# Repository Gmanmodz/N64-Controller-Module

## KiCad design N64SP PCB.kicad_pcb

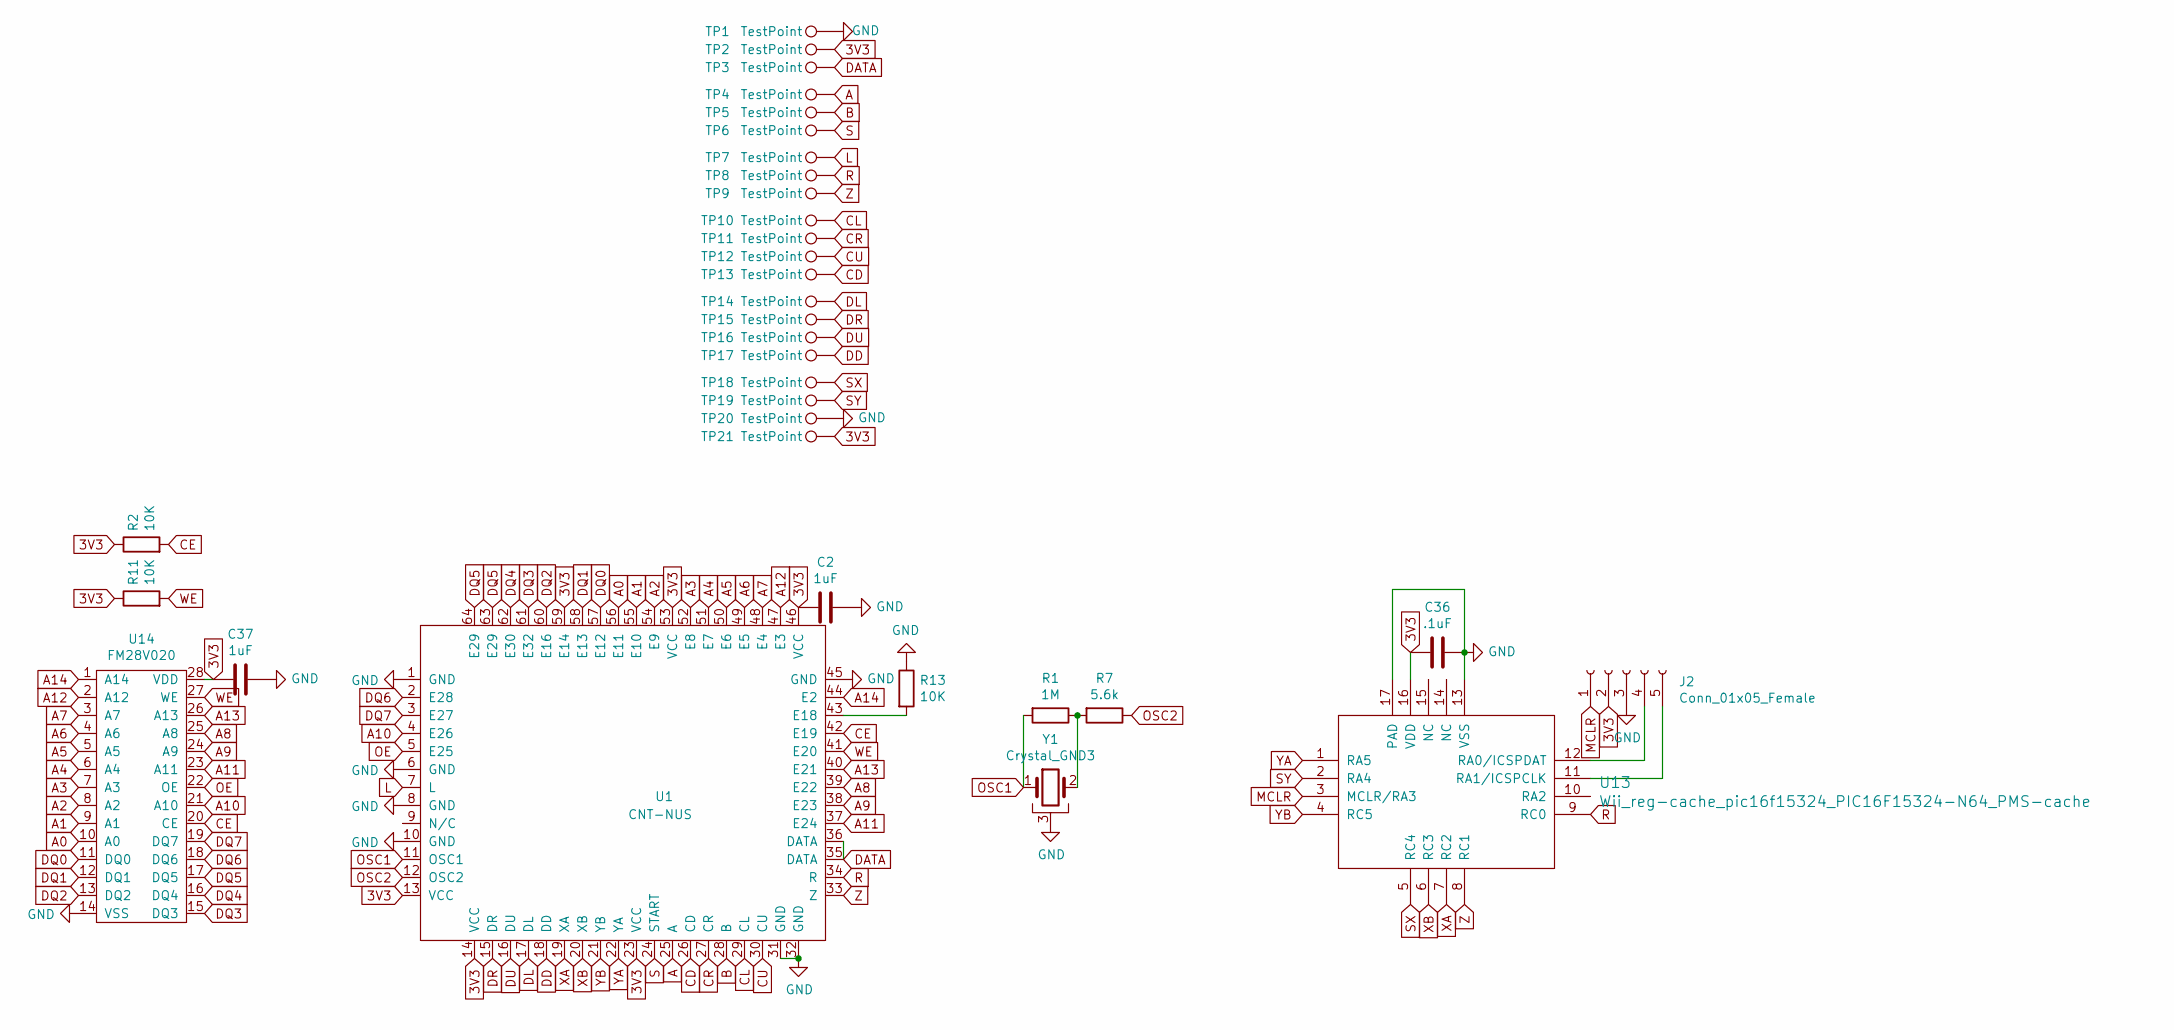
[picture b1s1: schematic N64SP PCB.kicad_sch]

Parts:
C2, C37: 1uF; C_0402_custom
C36: .1uF; C_0402_custom
J2: Conn_01x05_Female; PinHeader_1x05_P2.54mm_Vertical
R1: 1M; R_0402_custom
R2, R11, R13: 10K; R_0402_custom
R7: 5.6k; R_0402_custom
TP1, TP2, TP3, TP4, TP5, TP6, TP7, TP8, TP9, TP10, TP11, TP12, TP13, TP14, TP15, TP16, TP17, TP18, TP19, TP20, TP21: TestPoint; pad_castellated1
U1: CNT-NUS
U13: Wii_reg-cache_pic16f15324_PIC16F15324-N64_PMS-cac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; QFN-16-1EP_4x4mm_P0.65mm_EP2.1x2.1mm
U14: FM28V020; SOIC-28W_7.5x17.9mm_P1.27mm
Y1: Crystal_GND3; NUS-OSC

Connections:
3V3: C2.2, C36.2, C37.2, J2.2, R2.1, R11.1, TP2.1, TP21.1, U1.13 (VCC), U1.14 (VCC), U1.23 (VCC), U1.46 (VCC), U1.53 (VCC), U1.59 (E14), U13.16 (VDD), U14.28 (VDD)
A: TP4.1, U1.25 (A)
A0: U1.56 (E11), U14.10 (A0)
A1: U1.55 (E10), U14.9 (A1)
A2: U1.54 (E9), U14.8 (A2)
A3: U1.52 (E8), U14.7 (A3)
A4: U1.51 (E7), U14.6 (A4)
A5: U1.50 (E6), U14.5 (A5)
A6: U1.49 (E5), U14.4 (A6)
A7: U1.48 (E4), U14.3 (A7)
A8: U1.39 (E22), U14.25 (A8)
A9: U1.38 (E23), U14.24 (A9)
A10: U1.4 (E26), U14.21 (A10)
A11: U1.37 (E24), U14.23 (A11)
A12: U1.47 (E3), U14.2 (A12)
A13: U1.40 (E21), U14.26 (A13)
A14: U1.44 (E2), U14.1 (A14)
B: TP5.1, U1.28 (B)
CD: TP13.1, U1.26 (CD)
CE: R2.2, U1.42 (E19), U14.20 (CE)
CL: TP10.1, U1.29 (CL)
CR: TP11.1, U1.27 (CR)
CU: TP12.1, U1.30 (CU)
DATA: TP3.1, U1.35 (DATA), U1.36 (DATA)
DD: TP17.1, U1.18 (DD)
DL: TP14.1, U1.17 (DL)
DQ0: U1.57 (E12), U14.11 (DQ0)
DQ1: U1.58 (E13), U14.12 (DQ1)
DQ2: U1.60 (E16), U14.13 (DQ2)
DQ3: U1.61 (E32), U14.15 (DQ3)
DQ4: U1.62 (E30), U14.16 (DQ4)
DQ5: U1.63 (E29), U1.64 (E29), U14.17 (DQ5)
DQ6: U1.2 (E28), U14.18 (DQ6)
DQ7: U1.3 (E27), U14.19 (DQ7)
DR: TP15.1, U1.15 (DR)
DU: TP16.1, U1.16 (DU)
GND: C2.1, C36.1, C37.1, J2.3, R13.1, TP1.1, TP20.1, U1.1 (GND), U1.6 (GND), U1.8 (GND), U1.10 (GND), U1.31 (GND), U1.32 (GND), U1.45 (GND), U13.13 (VSS), U13.17 (PAD), U14.14 (VSS), Y1.3
L: TP7.1, U1.7 (L)
MCLR: J2.1, U13.3 (MCLR/RA3)
unnamed: J2.4, U13.12 (RA0/ICSPDAT)
unnamed: J2.5, U13.11 (RA1/ICSPCLK)
unnamed: R1.1, R7.2, Y1.2
unnamed: R13.2, U1.43 (E18)
OE: U1.5 (E25), U14.22 (OE)
OSC1: R1.2, U1.11 (OSC1), Y1.1
OSC2: R7.1, U1.12 (OSC2)
R: TP8.1, U1.34 (R), U13.9 (RC0)
S: TP6.1, U1.24 (START)
SX: TP18.1, U13.5 (RC4)
SY: TP19.1, U13.2 (RA4)
WE: R11.2, U1.41 (E20), U14.27 (WE)
XA: U1.19 (XA), U13.7 (RC2)
XB: U1.20 (XB), U13.6 (RC3)
YA: U1.22 (YA), U13.1 (RA5)
YB: U1.21 (YB), U13.4 (RC5)
Z: TP9.1, U1.33 (Z), U13.8 (RC1)

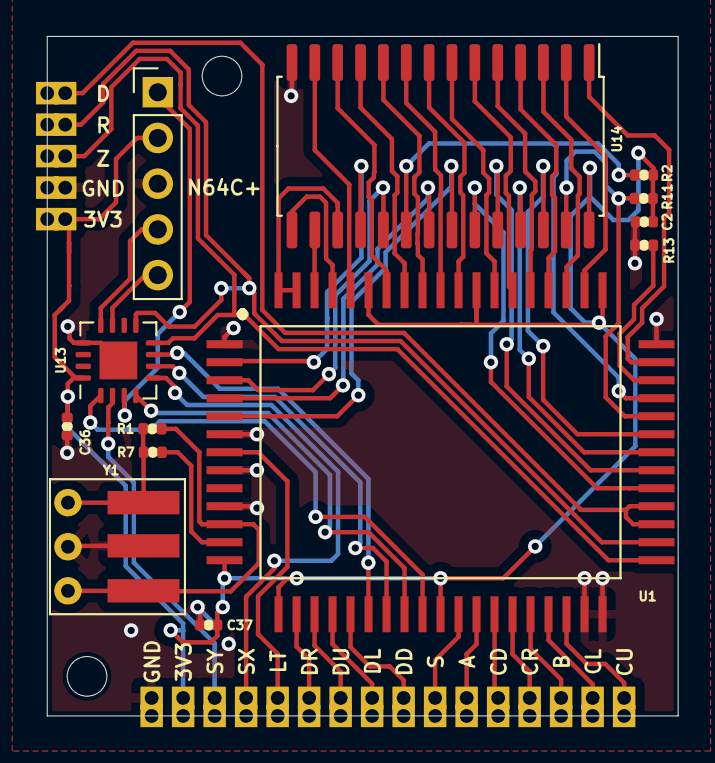
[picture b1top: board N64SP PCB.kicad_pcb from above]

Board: 2 copper layers, 35.0 x 37.7 mm, 34 parts (0 on the bottom side), 56 nets.

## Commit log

2024-03-10 added Kicad project
2024-03-23 added gerber for no castellizaed pads
